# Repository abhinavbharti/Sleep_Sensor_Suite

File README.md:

# Sleep Sensor Suite
This repository contains PCB designs for wireless ECG, EEG and EMG boards I developed for building a sensor suite for Sleep Reaseach.

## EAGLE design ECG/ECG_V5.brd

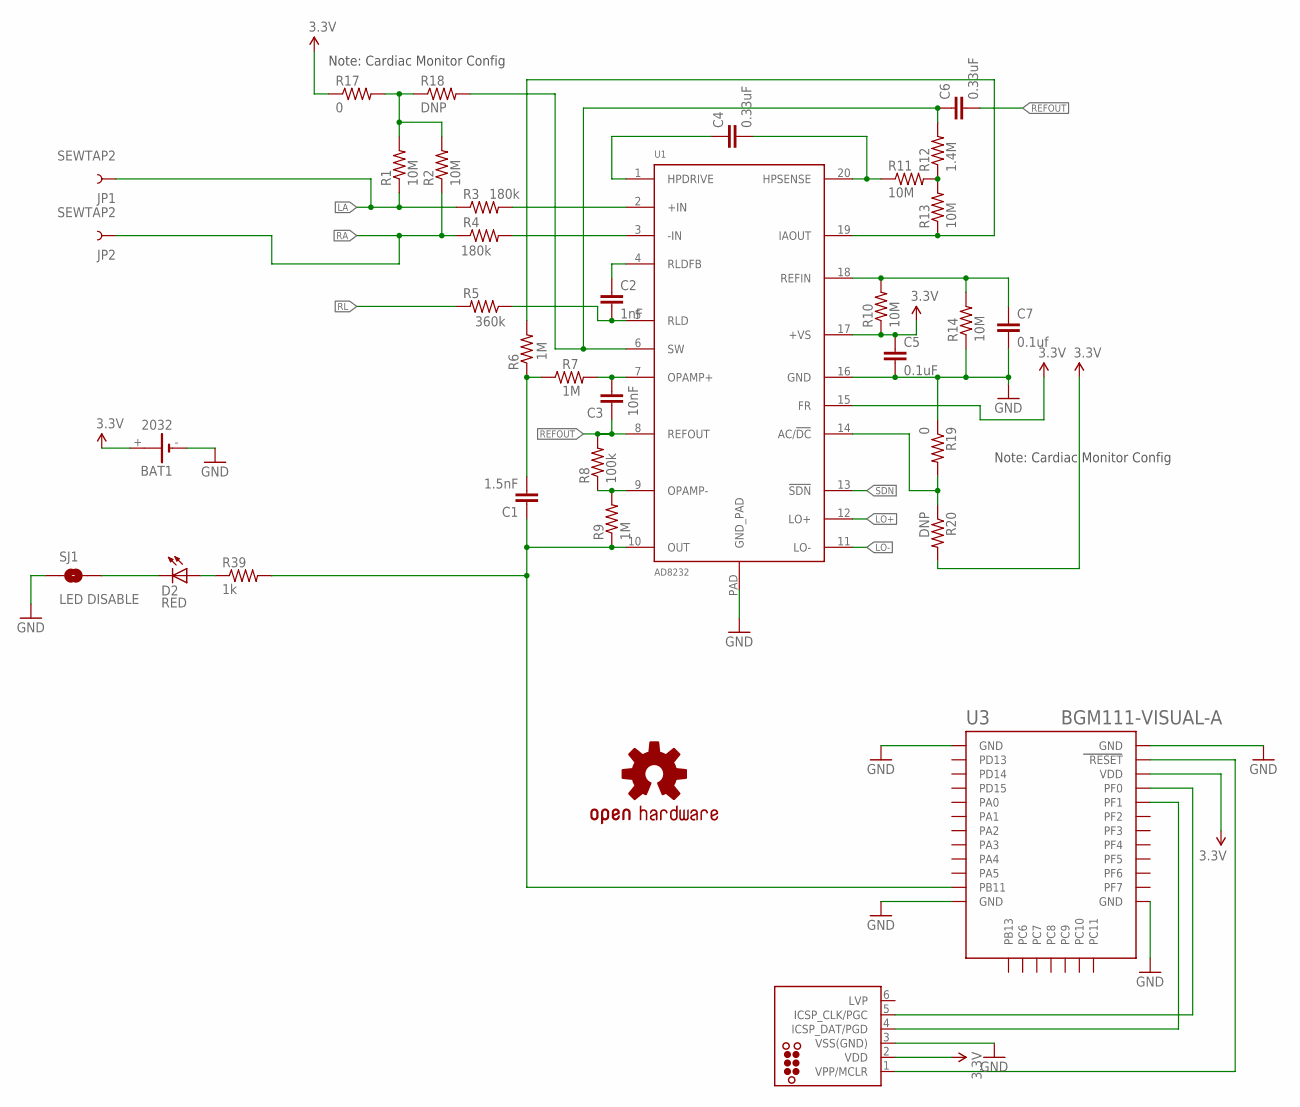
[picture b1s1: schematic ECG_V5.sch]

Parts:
BAT1: 2032; KZH20SMD
C1: 1.5nF; 0603-CAP
C2: 1nF; 0603-CAP
C3: 10nF; 0603-CAP
C4, C6: 0.33uF; 0805
C5: 0.1uF; 0603-CAP
C7: 0.1uf; 0603-CAP
D2: RED; LED-0603
J2: TC2030-MCP-NL
JP1, JP2: SEWTAP2; PETAL-LONG-2
LOGO1: OSHW-LOGOS; OSHW-LOGO-S
R1, R2, R10, R11, R13, R14: 10M; 0603-RES
R3, R4: 180k; 0603-RES
R5: 360k; 0603-RES
R6, R7, R9: 1M; 0603-RES
R8: 100k; 0603-RES
R12: 1.4M; 0603-RES
R17, R19: 0; 0603
R18, R20: DNP; 0603
R39: 1k; 0603-RES
SJ1: LED DISABLE; SJ_2S-TRACE
U1: AD8232; LFCSP_20
U3: BGM111-VISUAL-A; BGM111-A

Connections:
3.3V: BAT1.+, C5.1, J2.2 (VDD), R10.1, R17.1, R20.2, U1.15 (FR), U1.17 (+VS), U3.VDD
GND: BAT1.-, C5.2, C7.2, J2.3 (VSS(GND)), R14.1, R19.1, SJ1.1, U1.16 (GND), U1.PAD (GND_PAD), U3.GND, U3.GND@2 (GND), U3.GND@3 (GND), U3.GND@4 (GND)
LA: JP1.1, R1.1, R3.1
LO+: U1.12 (LO+)
LO-: U1.11 (LO-)
unnamed: R3.2, U1.2 (+IN)
unnamed: R4.2, U1.3 (-IN)
unnamed: C3.2, R7.2, U1.7 (OPAMP+)
unnamed: C4.2, R11.1, U1.20 (HPSENSE)
unnamed: C7.1, R10.2, R14.2, U1.18 (REFIN)
unnamed: R8.1, R9.2, U1.9 (OPAMP-)
unnamed: R6.2, R13.1, U1.19 (IAOUT)
unnamed: C1.2, R6.1, R7.1
unnamed: R19.2, R20.1, U1.14 (AC/!DC)
unnamed: C4.1, U1.1 (HPDRIVE)
unnamed: R11.2, R12.1, R13.2
unnamed: C6.1, R12.2, R18.2, U1.6 (SW)
unnamed: C2.1, U1.4 (RLDFB)
unnamed: C2.2, R5.1, U1.5 (RLD)
unnamed: R1.2, R2.2, R17.2, R18.1
unnamed: J2.1 (VPP/MCLR), U3.RESET
unnamed: J2.5 (ICSP_CLK/PGC), U3.PF0
unnamed: J2.4 (ICSP_DAT/PGD), U3.PF1
unnamed: D2.A, R39.1
unnamed: D2.C, SJ1.2
RA: JP2.1, R2.1, R4.1
REFOUT: C3.1, C6.2, R8.2, U1.8 (REFOUT)
RL: R5.2
SDN: U1.13 (!SDN)
SIGNAL_OUT: C1.1, R9.1, R39.2, U1.10 (OUT), U3.PB11

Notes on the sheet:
Note: Cardiac Monitor Config

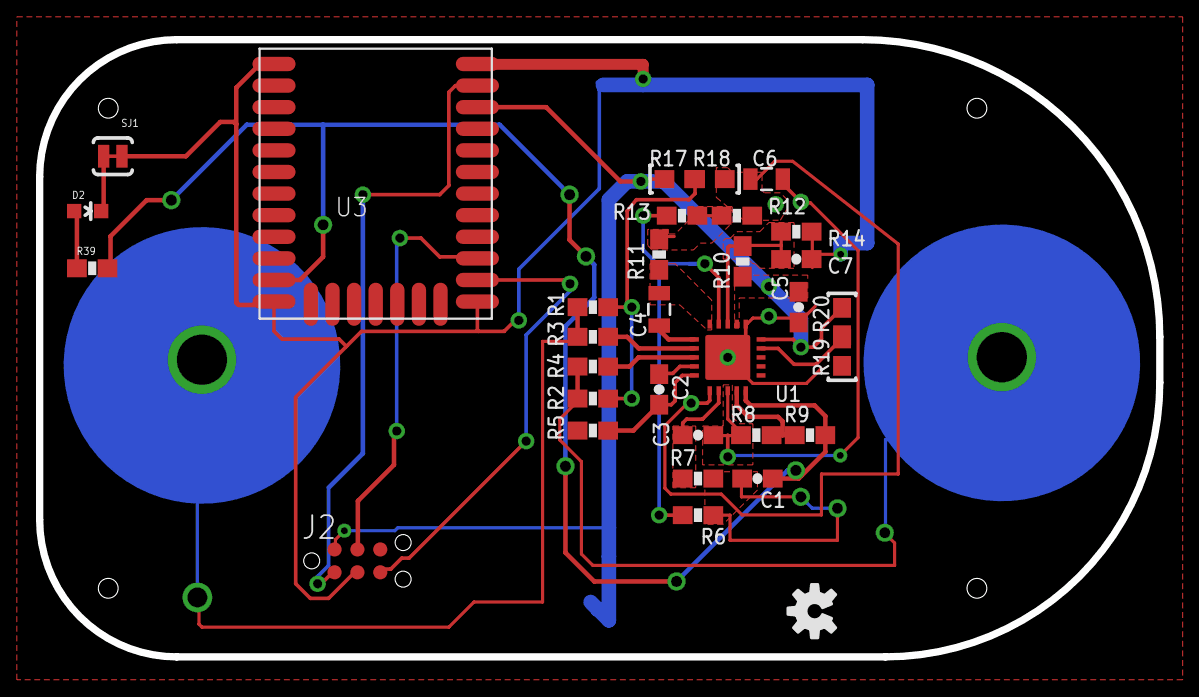
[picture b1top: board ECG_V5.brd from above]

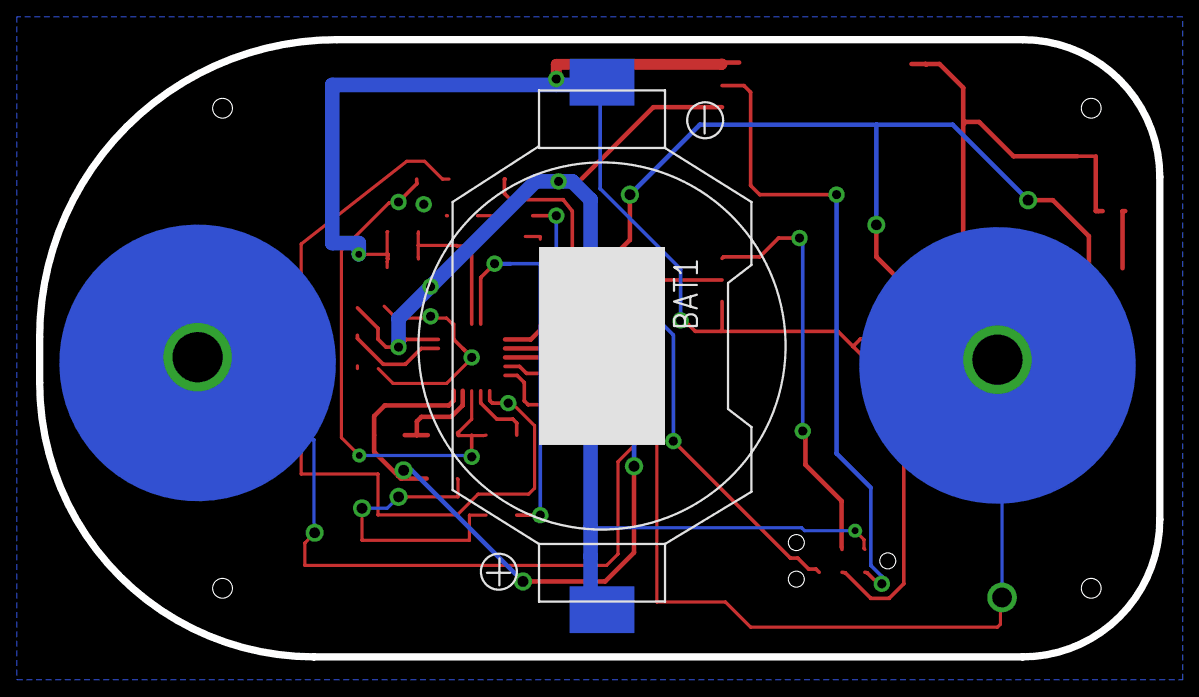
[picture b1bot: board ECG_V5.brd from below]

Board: 2 copper layers, 62.2 x 34.3 mm, 35 parts (3 on the bottom side), 26 nets.

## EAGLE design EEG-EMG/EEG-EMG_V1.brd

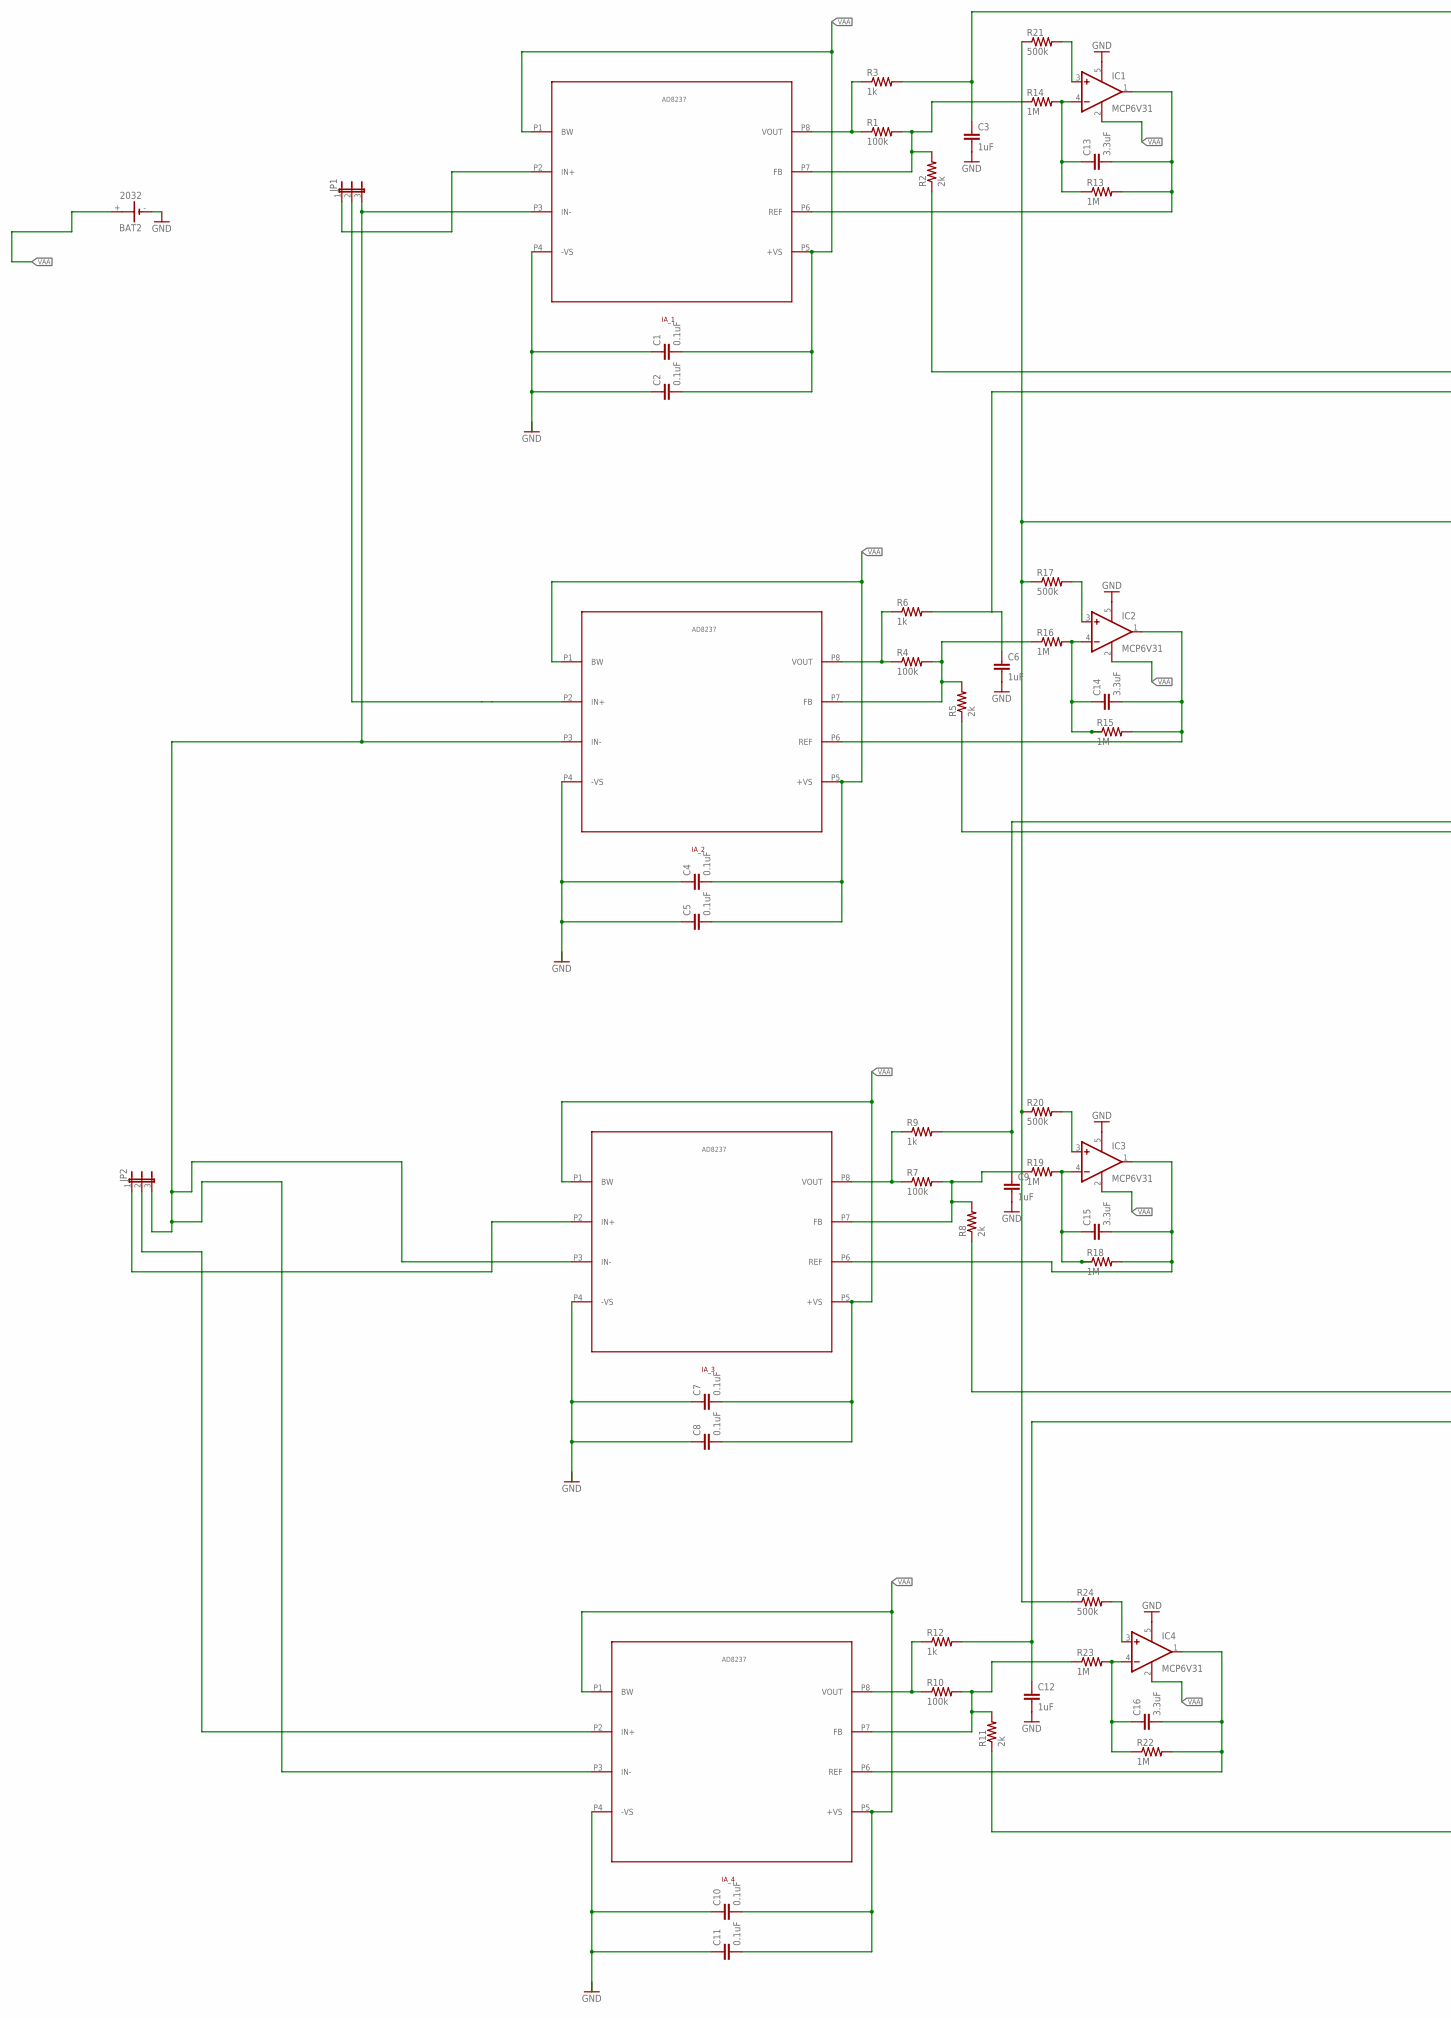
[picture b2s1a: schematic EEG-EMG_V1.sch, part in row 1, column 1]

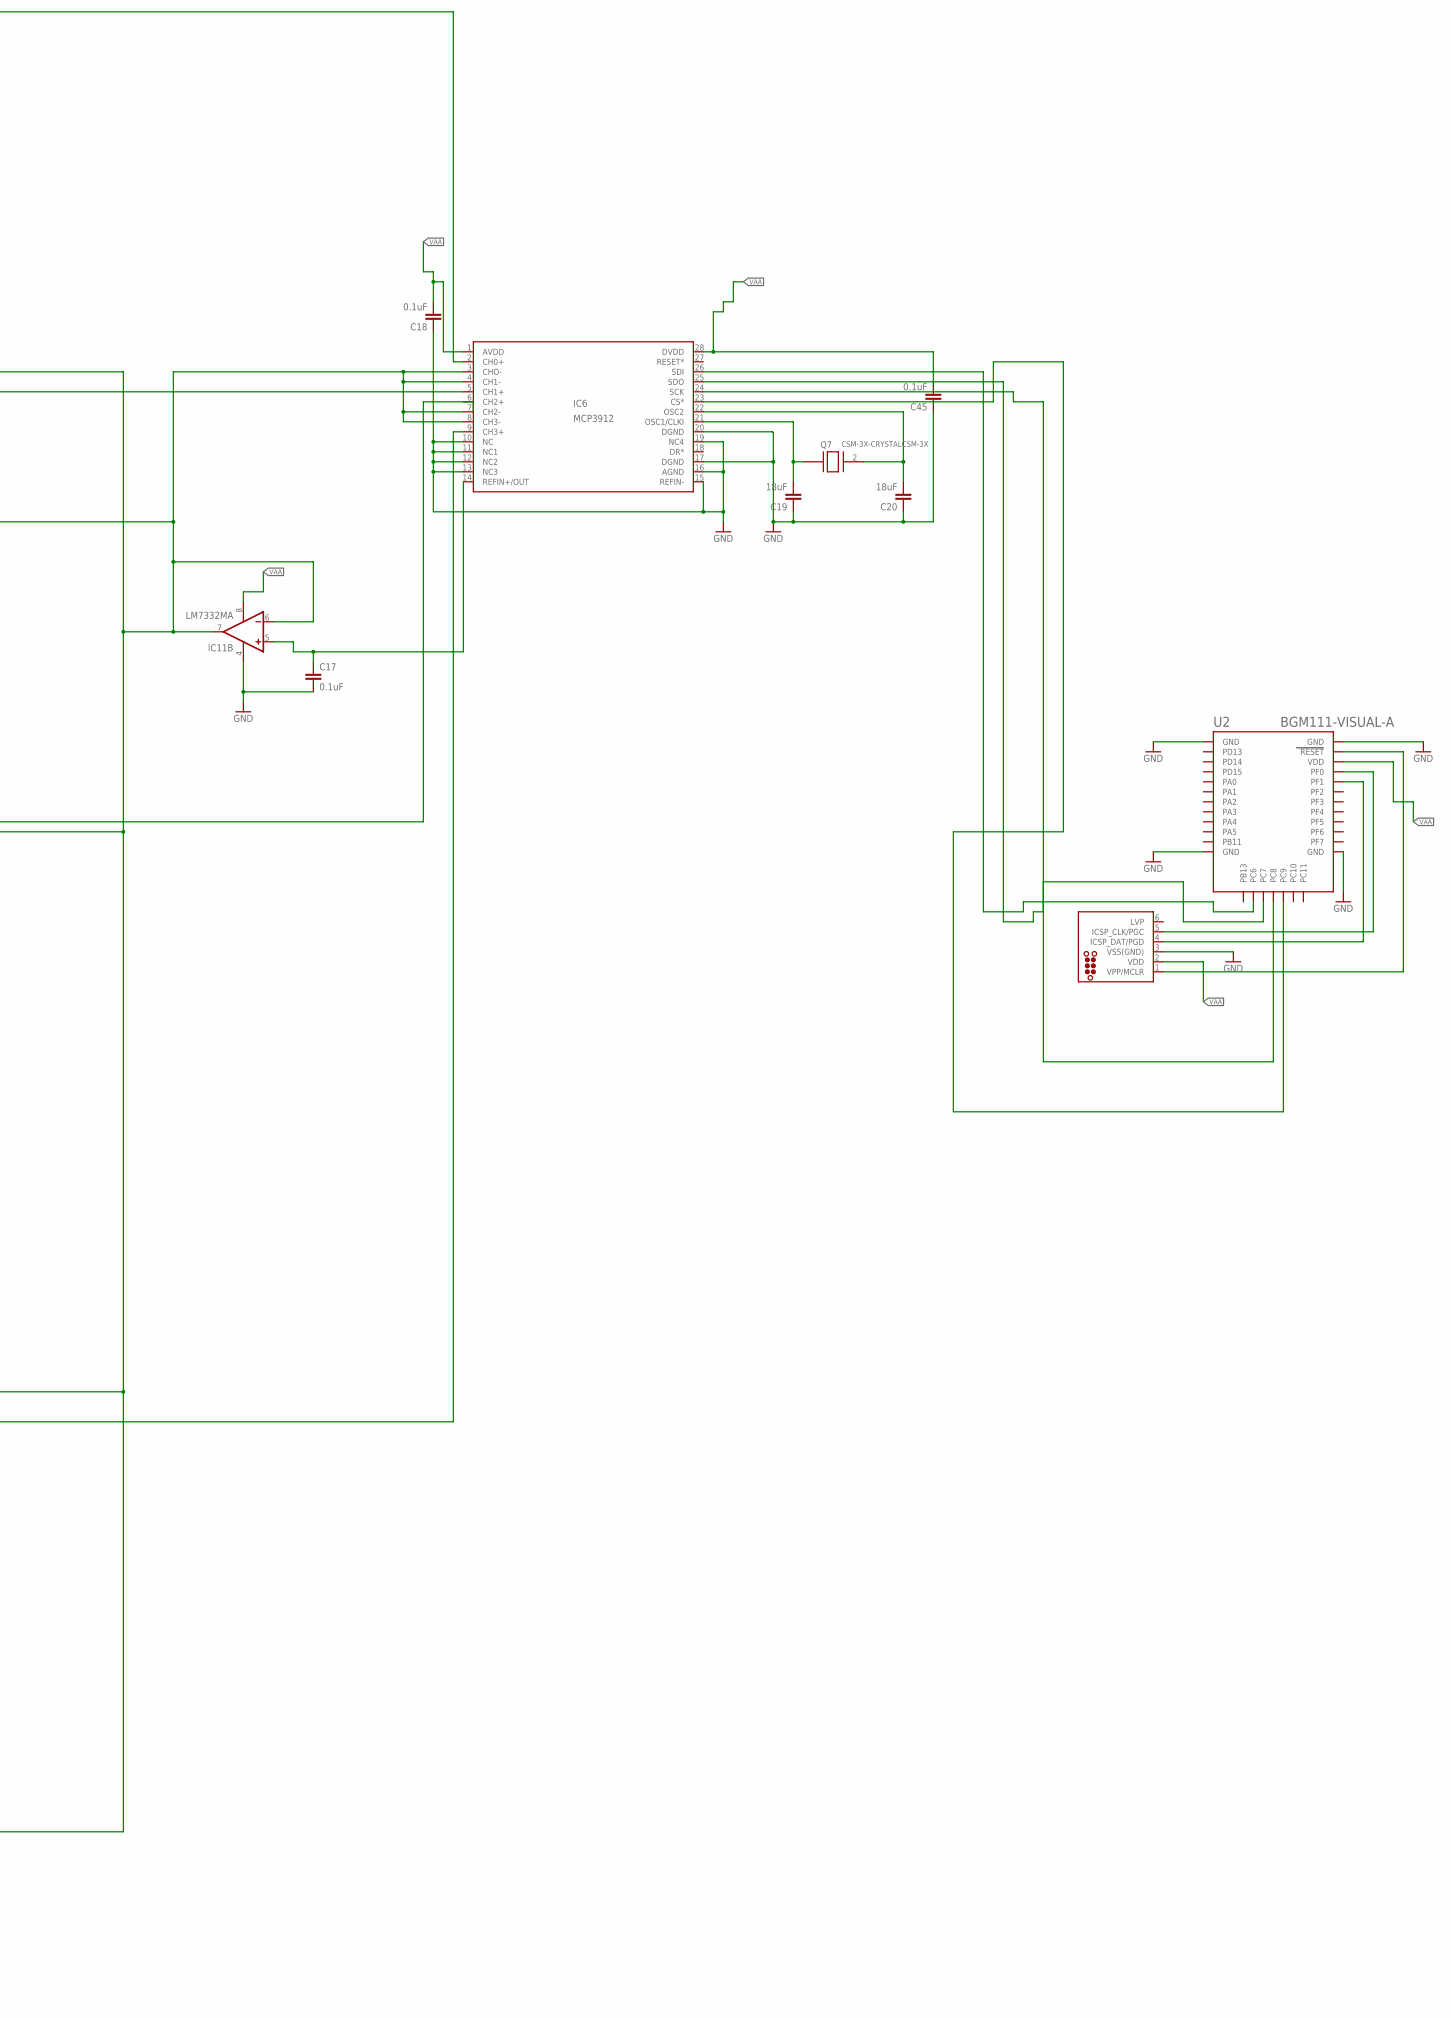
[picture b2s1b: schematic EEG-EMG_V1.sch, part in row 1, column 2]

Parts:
BAT2: 2032; KZH20SMD
C1, C2, C4, C5, C7, C8, C10, C11, C17, C18, C45: 0.1uF; 0805
C3, C6, C9, C12: 1uF; 0805
C13, C14, C15, C16: 3.3uF; 0805
C19, C20: 18uF; 0805
IA_1, IA_2, IA_3, IA_4: AD8237; MSOP8
IC1, IC2, IC3, IC4: MCP6V31; SOT23-5
IC6: MCP3912; SSOP28
IC11: LM7332MA; SO08
J2: TC2030-MCP-NL
JP1, JP2: JP2W
Q7: CSM-3X-CRYSTALCSM-3X; CSM-3X
R1, R4, R7, R10: 100k; 0805
R2, R5, R8, R11: 2k; 0805
R3, R6, R9, R12: 1k; 0805
R13, R14, R15, R16, R18, R19, R22, R23: 1M; 0805
R17, R20, R21, R24: 500k; 0805
U2: BGM111-VISUAL-A; BGM111-A

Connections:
EEG1+: IA_1.P2 (IN+), JP1.1
EEG2+: IA_2.P2 (IN+), JP1.2
EMG1+: IA_3.P2 (IN+), JP2.1
EMG2+: IA_4.P2 (IN+), JP2.2
GND: BAT2.-, C1.1, C2.1, C3.2, C4.1, C5.1, C6.2, C7.1, C8.1, C9.2, C10.1, C11.1, C12.2, C17.2, C18.1, C19.1, C20.1, C45.1, IA_1.P4 (-VS), IA_2.P4 (-VS), IA_3.P4 (-VS), IA_4.P4 (-VS), IC1.5 (V+), IC2.5 (V+), IC3.5 (V+), IC4.5 (V+), IC6.10 (NC), IC6.11 (NC1), IC6.12 (NC2), IC6.13 (NC3), IC6.15 (REFIN-), IC6.16 (AGND), IC6.17 (DGND), IC6.19 (NC4), IC6.20 (DGND), IC11.4 (V-), J2.3 (VSS(GND)), U2.GND, U2.GND@2 (GND), U2.GND@3 (GND), U2.GND@4 (GND)
unnamed: IA_1.P8 (VOUT), R1.1, R3.1
unnamed: IA_1.P7 (FB), R1.2, R2.2, R14.1
unnamed: C3.1, IC6.2 (CH0+), R3.2
unnamed: IA_2.P8 (VOUT), R4.1, R6.1
unnamed: IA_2.P7 (FB), R4.2, R5.2, R16.1
unnamed: C6.1, IC6.5 (CH1+), R6.2
unnamed: IA_3.P8 (VOUT), R7.1, R9.1
unnamed: IA_3.P7 (FB), R7.2, R8.2, R19.1
unnamed: C9.1, R9.2
unnamed: IA_4.P8 (VOUT), R10.1, R12.1
unnamed: IA_4.P7 (FB), R10.2, R11.2, R23.1
unnamed: C12.1, IC6.9 (CH3+), R12.2
unnamed: C13.1, IC1.4 (-IN), R13.1, R14.2
unnamed: C13.2, IA_1.P6 (REF), IC1.1 (OUT), R13.2
unnamed: C17.1, IC6.14 (REFIN+/OUT), IC11.5 (+IN)
unnamed: C14.1, IC2.4 (-IN), R15.1, R16.2
unnamed: C14.2, IA_2.P6 (REF), IC2.1 (OUT), R15.2
unnamed: IC6.3 (CHO-), IC6.4 (CH1-), IC6.7 (CH2-), IC6.8 (CH3-), IC11.6 (-IN), IC11.7 (OUT), R2.1, R5.1, R8.1, R11.1, R17.1, R20.1, R21.1, R24.1
unnamed: C15.1, IC3.4 (-IN), R18.1, R19.2
unnamed: C15.2, IA_3.P6 (REF), IC3.1 (OUT), R18.2
unnamed: IC2.3 (+IN), R17.2
unnamed: C16.1, IC4.4 (-IN), R22.1, R23.2
unnamed: C16.2, IA_4.P6 (REF), IC4.1 (OUT), R22.2
unnamed: IC3.3 (+IN), R20.2
unnamed: IC1.3 (+IN), R21.2
unnamed: IC4.3 (+IN), R24.2
unnamed: IC6.26 (SDI), U2.PC6
unnamed: IC6.25 (SDO), U2.PC7
unnamed: IC6.24 (SCK), U2.PC8
unnamed: IC6.23 (CS*), U2.PC9
unnamed: J2.1 (VPP/MCLR), U2.RESET
unnamed: J2.5 (ICSP_CLK/PGC), U2.PF0
unnamed: J2.4 (ICSP_DAT/PGD), U2.PF1
unnamed: C19.2, IC6.21 (OSC1/CLKI), Q7.1
unnamed: C20.2, IC6.22 (OSC2), Q7.2
REF: IA_1.P3 (IN-), IA_2.P3 (IN-), IA_3.P3 (IN-), IA_4.P3 (IN-), JP1.3, JP2.3
VAA: BAT2.+, C1.2, C2.2, C4.2, C5.2, C7.2, C8.2, C10.2, C11.2, C18.2, C45.2, IA_1.P1 (BW), IA_1.P5 (+VS), IA_2.P1 (BW), IA_2.P5 (+VS), IA_3.P1 (BW), IA_3.P5 (+VS), IA_4.P1 (BW), IA_4.P5 (+VS), IC1.2 (V-), IC2.2 (V-), IC3.2 (V-), IC4.2 (V-), IC6.1 (AVDD), IC6.28 (DVDD), IC11.8 (V+)
VDD: J2.2 (VDD), U2.VDD

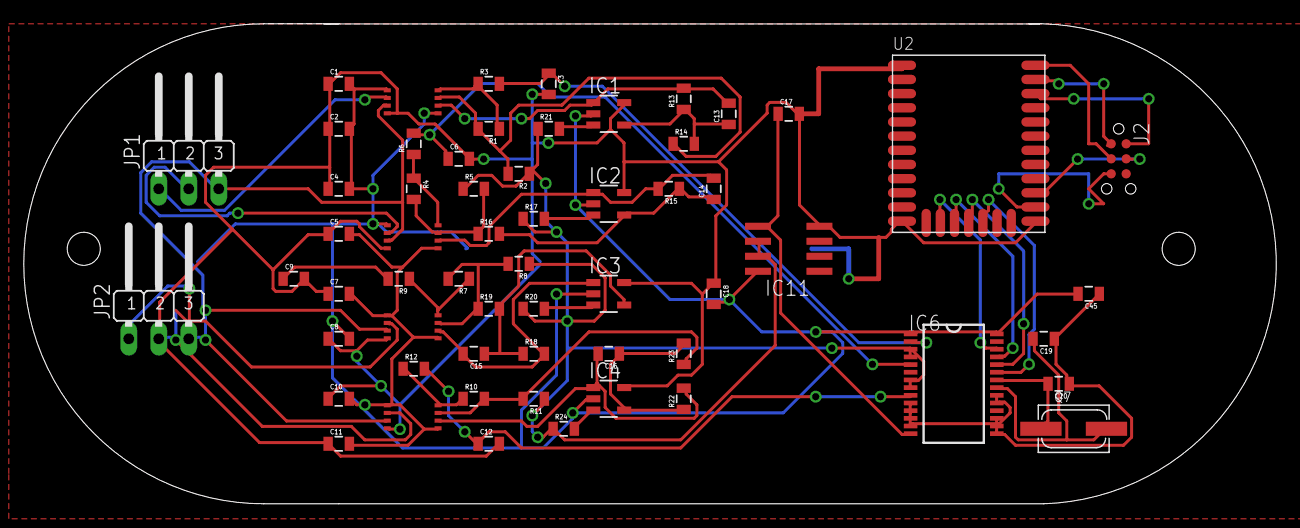
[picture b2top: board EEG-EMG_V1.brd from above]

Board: 2 copper layers, 106.0 x 40.6 mm, 61 parts (1 on the bottom side), 43 nets.

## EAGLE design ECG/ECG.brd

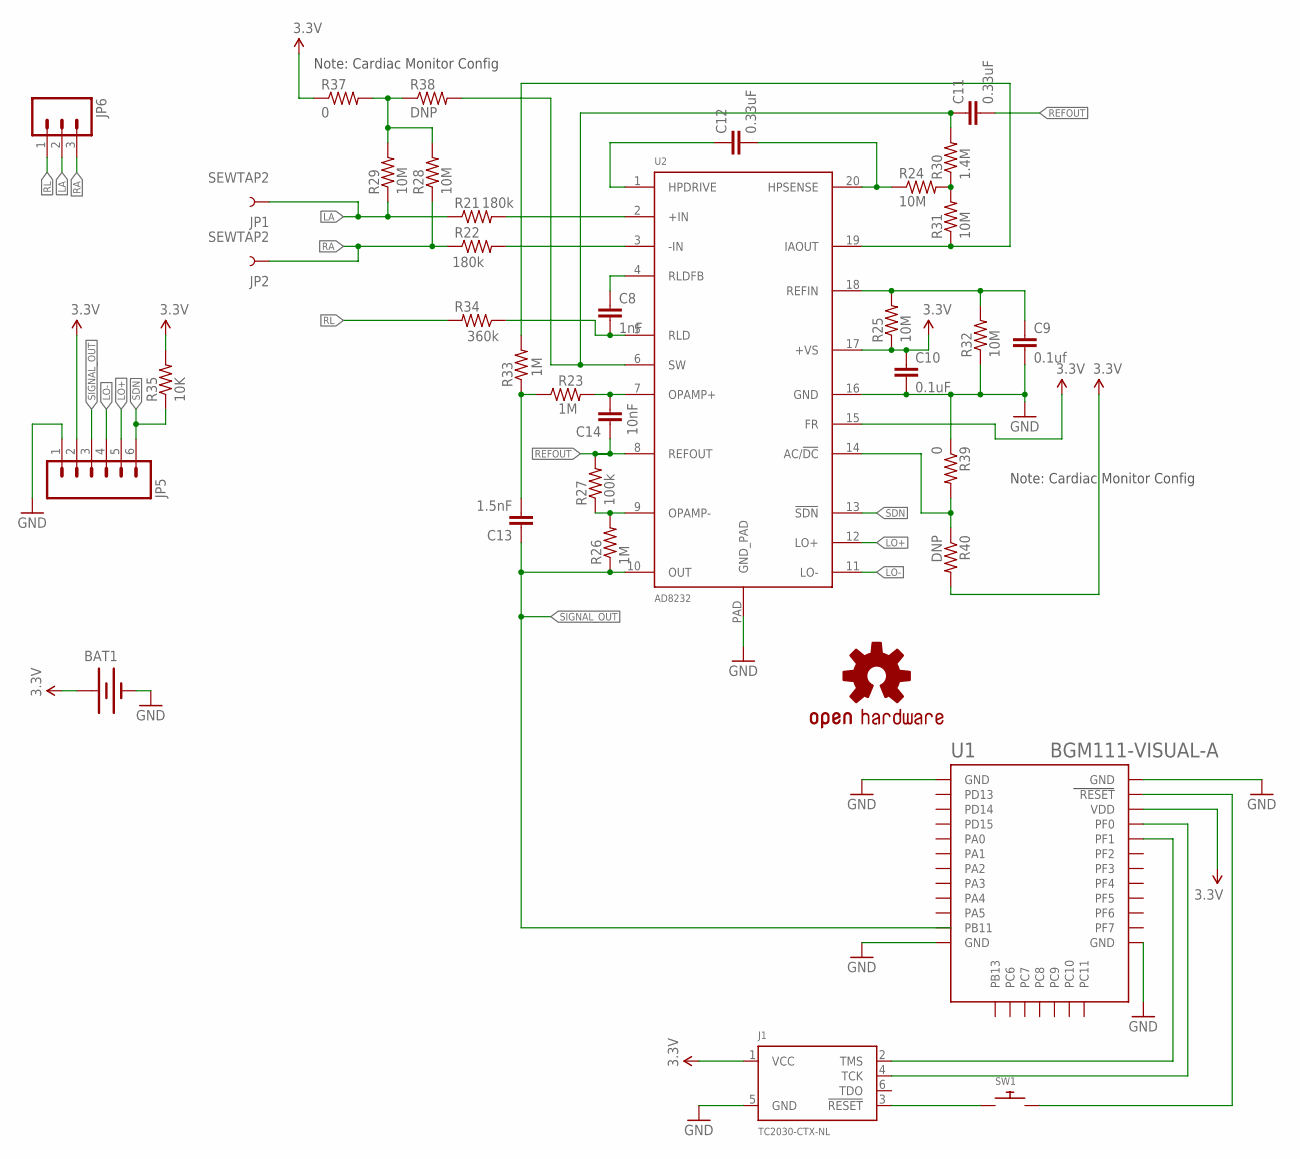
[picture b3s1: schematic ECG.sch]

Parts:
BAT1: BATTERY20SMD; BATTCON_20MM
C8: 1nF; 0603-CAP
C9: 0.1uf; 0603-CAP
C10: 0.1uF; 0603-CAP
C11, C12: 0.33uF; 0805
C13: 1.5nF; 0603-CAP
C14: 10nF; 0603-CAP
J1: TC2030-CTX-NL; TC2030-IDC-NL
JP1, JP2: SEWTAP2; PETAL-LONG-2
JP5: M06SIP; 1X06
JP6: M03PTH; 1X03
LOGO3: OSHW-LOGOS; OSHW-LOGO-S
R21, R22: 180k; 0603-RES
R23, R26, R33: 1M; 0603-RES
R24, R25, R28, R29, R31, R32: 10M; 0603-RES
R27: 100k; 0603-RES
R30: 1.4M; 0603-RES
R34: 360k; 0603-RES
R35: 10K; 0603-RES
R37, R39: 0; 0603
R38, R40: DNP; 0603
SW1: SWITCH_PUSHBUTTONSOFTTOUCHSMD_SJ; PUSHBUTTON_SMD_SJ
U1: BGM111-VISUAL-A; BGM111-A
U2: AD8232; LFCSP_20

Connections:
3.3V: BAT1.1 (+), C10.1, J1.1 (VCC), JP5.2, R25.1, R35.2, R37.1, R40.2, U1.VDD, U2.15 (FR), U2.17 (+VS)
GND: BAT1.2 (-), C9.2, C10.2, J1.5 (GND), JP5.1, R32.1, R39.1, U1.GND, U1.GND@2 (GND), U1.GND@3 (GND), U1.GND@4 (GND), U2.16 (GND), U2.PAD (GND_PAD)
LA: JP1.1, JP6.2, R21.1, R29.1
LO+: JP5.5, U2.12 (LO+)
LO-: JP5.4, U2.11 (LO-)
unnamed: J1.3 (!RESET), SW1.P$1
unnamed: SW1.P$2, U1.RESET
unnamed: J1.4 (TCK), U1.PF0
unnamed: J1.2 (TMS), U1.PF1
unnamed: R21.2, U2.2 (+IN)
unnamed: R22.2, U2.3 (-IN)
unnamed: C14.2, R23.2, U2.7 (OPAMP+)
unnamed: C12.2, R24.1, U2.20 (HPSENSE)
unnamed: C9.1, R25.2, R32.2, U2.18 (REFIN)
unnamed: R26.2, R27.1, U2.9 (OPAMP-)
unnamed: C12.1, U2.1 (HPDRIVE)
unnamed: R24.2, R30.1, R31.2
unnamed: C11.1, R30.2, R38.2, U2.6 (SW)
unnamed: C8.1, U2.4 (RLDFB)
unnamed: C13.2, R23.1, R33.1
unnamed: C8.2, R34.1, U2.5 (RLD)
unnamed: R31.1, R33.2, U2.19 (IAOUT)
unnamed: R28.2, R29.2, R37.2, R38.1
unnamed: R39.2, R40.1, U2.14 (AC/!DC)
RA: JP2.1, JP6.3, R22.1, R28.1
REFOUT: C11.2, C14.1, R27.2, U2.8 (REFOUT)
RL: JP6.1, R34.2
SDN: JP5.6, R35.1, U2.13 (!SDN)
SIGNAL_OUT: C13.1, JP5.3, R26.1, U2.10 (OUT)

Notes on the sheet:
Note: Cardiac Monitor Config

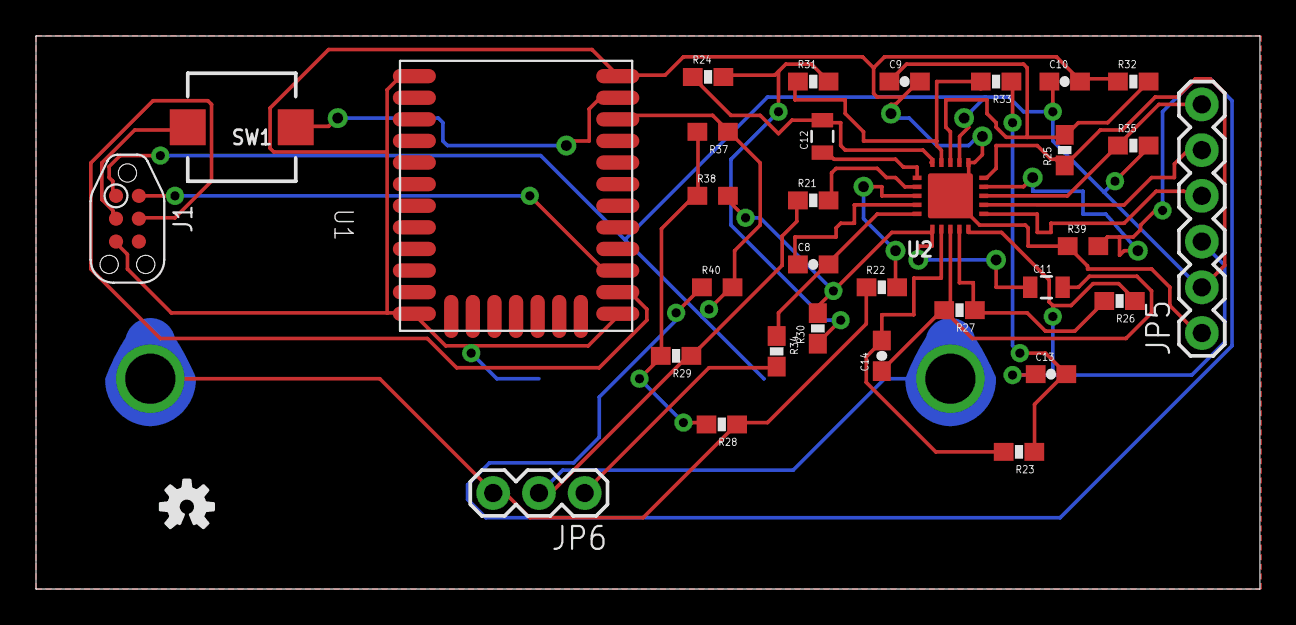
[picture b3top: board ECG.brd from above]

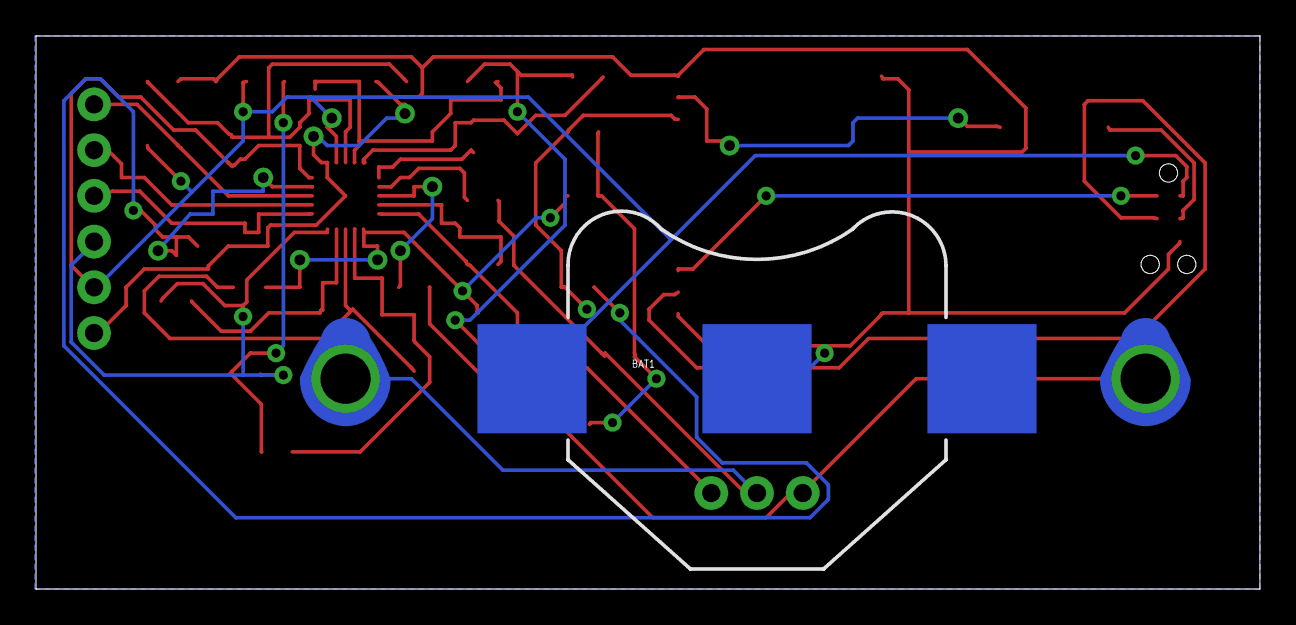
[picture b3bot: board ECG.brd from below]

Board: 2 copper layers, 68.0 x 30.7 mm, 36 parts (3 on the bottom side), 29 nets.

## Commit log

2016-10-02 Deleted README.md
2016-10-09 Intial Schematic for New ECG Board
2016-10-09 Added BGM111
2016-10-09 Added Tag Connector for Programming/Debugging BGM111
2016-10-10 Added Batteryholder and snap connectors for RA,LA
2016-10-11 Removed previous files
2016-10-13 Started ECG BRD.
2016-10-13 Initial Layout for the Board
2016-10-23 Deleted all redundant files
2016-10-23 Added Routed Board
2016-10-23 Added Ground Planes to Board
2016-10-23 Lock Deleted
2016-11-07 Added modified schematic for ECG Board
2016-11-07 Error while pushing
2016-11-08 Added modified ECG Schematic and Board , Version 2
2016-11-08 DRC error correction
2016-11-09 Added new tag connect component and corrected pin configuation
2016-11-21 Corrected the Supply issue with tag connect and changed width of some routes
2016-11-21 Changed the copper pads for sewtap
2016-11-28 Added 4 input stage amplifiers- AD8237
2016-11-28 Added MCP6v31U
2016-11-28 Imported Components MCP3912 & LM7332MA
2016-11-28 Completed connections to all 4 Instrumentation Amplifiers
2016-11-28 Completed connections to MCP3912
2016-11-28 Added Bluetooth Module BGM111
2016-11-28 Completed Schematic
2016-11-28 Completed Board
2016-11-28 Added Presentation
2016-11-30 Schematic for Version 3 ECG
2016-11-30 Completed the Version 3 of ECG Board
2016-11-30 Added mounting holes
2016-11-30 Modified Sewtap pads and reduced board size
2016-11-30 Found two unrouted signals, routed them. Board Complete.
2016-12-02 Corrected thepolygon issues, thickened connections to pad and resolved clearance issues
2016-12-04 SPI Connections Done
2016-12-04 Changed EMG Jumper Connection
2016-12-04 Completed Board - Basic Functionality V1
2016-12-05 Updated Presentation
2017-01-19 Added the new board with Bluetooth module moved to the edge
2017-01-19 Added LED circuit
2017-01-19 Completed Routing
2017-01-19 Added Ground Plane
2017-01-23 Changed Ranks for ground pour from 1 to 6.
2017-01-23 Connections Debugged
2017-03-03 Made missing connection between AD8232 out to PB11 on bluetooth module
2017-03-10 Moved BGM111

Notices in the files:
parts and their libraries:
SparkFun-Electromechanical: Licensing: Creative Commons ShareAlike 4.0 International - https://creativecommons.org/licenses/by-sa/4.0
SparkFun-Passives: Licensing: CC v3.0 Share-Alike You are welcome to use this library for commercial purposes.
